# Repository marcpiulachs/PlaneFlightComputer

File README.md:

# Flight Computer

This project is a flight computer powered by an ESP32-C3 microcontroller, designed to control two motors and two servos. It integrates multiple sensors and supports a range of functionalities that make it suitable for small UAVs and drones. The system is designed to operate on a 300mAh LiPo battery, with built-in charging through USB-C.

## Features

- **ESP32-C3** microcontroller for reliable performance and wireless connectivity.
- **Motor Control:**
  - Motor 1: GPIO4
  - Motor 2: GPIO5
- **Servo Control:**
  - Servo 1: GPIO1
  - Servo 2: GPIO6
- **Sensors:**
  - **MAX17048G** (Fuel Gauge) on Address: `0x36` (00110110b)
  - **BMP388** (Barometric Pressure) on Address: `0x76` (1001100b)
  - **QMC5883L** (Magnetometer) on Address: `0x0d` (0001101b)
  - **ICM-42670-P** (6-axis IMU) on Address: `0x68` (1101000b)
- **LEDs:**
  - Internal LED: GPIO7
  - External LED: GPIO0
- **Battery:**
  - Recommended battery: **300mAh LiPo** for optimal performance
  - **USB-C charging** support for ease of use

## Recommended Hardware

- **Battery:** 300mAh LiPo
- **USB-C charger** (included)

## Pinout

| Component      | GPIO Pin  | Description                      |
|----------------|-----------|----------------------------------|
| Motor 1        | GPIO4     | Motor driver pin                 |
| Motor 2        | GPIO5     | Motor driver pin                 |
| Servo 1        | GPIO1     | Servo control pin                |
| Servo 2        | GPIO6     | Servo control pin                |
| Internal LED   | GPIO7     | Status indicator                 |
| External LED   | GPIO0     | Additional LED indicator         |
| MAX17048G      | I2C (0x36)| Fuel gauge sensor                |
| BMP388         | I2C (0x76)| Barometric pressure sensor       |
| QMC5883L       | I2C (0x0d)| Magnetometer sensor              |
| ICM-42670-P    | I2C (0x68)| 6-axis IMU sensor                |

## Power Management

The flight computer operates on a **300mAh LiPo battery**, which provides sufficient power for typical operations. For convenience, the board features **USB-C charging**, allowing you to charge the battery easily.

## Getting Started

To get started with the flight computer:

1. Connect the appropriate motors, servos, and sensors as listed in the pinout table.
2. Power the device using a 300mAh LiPo battery.
3. Use the onboard USB-C port to charge the battery when needed.

## License

This project is open source and available under the [MIT License](LICENSE).

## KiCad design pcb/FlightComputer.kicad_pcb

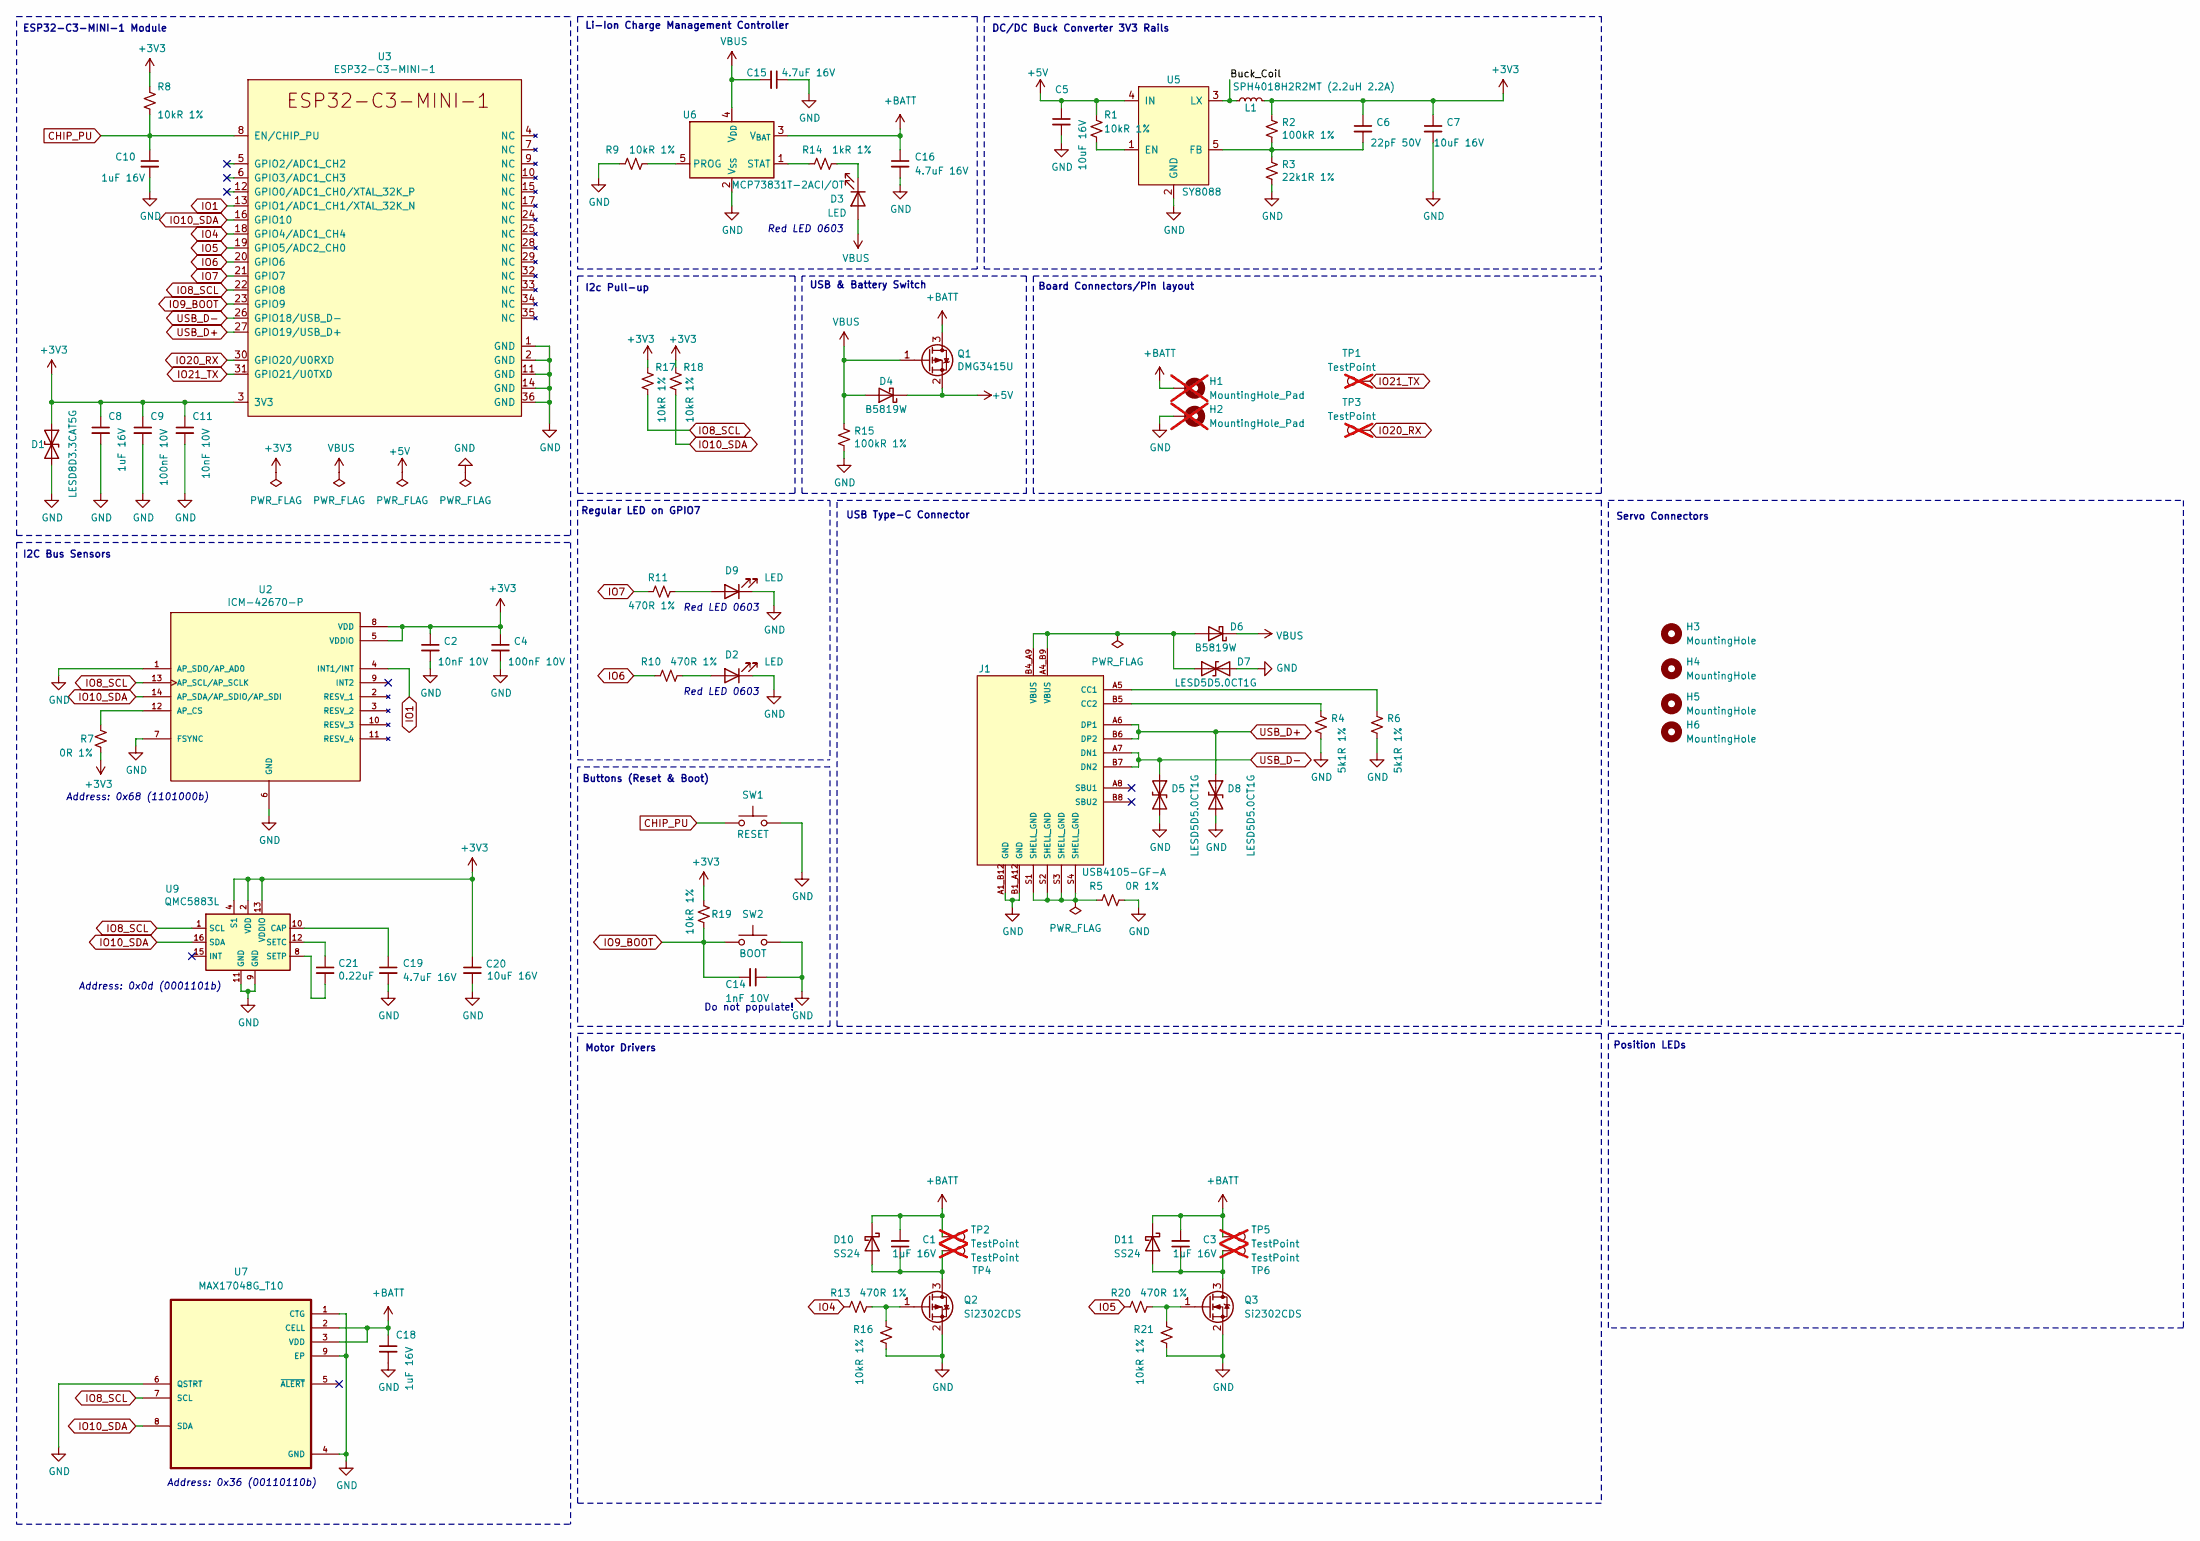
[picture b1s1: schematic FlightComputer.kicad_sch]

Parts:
C1, C3, C8, C10, C18: 1uF 16V; C_0402_1005Metric; LCSC C52923
C2, C11: 10nF 10V; C_0402_1005Metric; LCSC C15195
C4, C9: 100nF 10V; C_0402_1005Metric; LCSC C1525
C5, C7, C20: 10uF 16V; C_0805_2012Metric; LCSC C15850
C6: 22pF 50V; C_0603_1608Metric; LCSC C1653
C14: 1nF 10V; C_0402_1005Metric; LCSC C1523
C15, C16, C19: 4.7uF 16V; C_0603_1608Metric; LCSC C19666
C21: 0.22uF; C_0402_1005Metric; LCSC C16772
D1: LESD8D3.3CAT5G; D_SOD-882; LCSC C172409
D2, D3, D9: LED; LED_0603_1608Metric; LCSC C2286
D4, D6: B5819W; D_SOD-123; LCSC C8598
D5, D7, D8: LESD5D5.0CT1G; D_SOD-523; LCSC C383211
D10, D11: SS24; D_SOD-123; LCSC C5380709
H1, H2: MountingHole_Pad; TestPoint_Pad_D2.0mm; not fitted
H3, H4, H5, H6: MountingHole; MountingHole_2.2mm_M2_DIN965
J1: USB4105-GF-A; GCT_USB4105-GF-A; PARTREV A3; LCSC C165948
L1: SPH4018H2R2MT (2.2uH 2.2A); L_Bourns-SRN4018; LCSC C370436
Q1: DMG3415U; SOT-23; LCSC C96616
Q2, Q3: Si2302CDS; SOT-23; LCSC C10488
R1, R8, R9, R16, R17, R18, R19, R21: 10kR 1%; R_0402_1005Metric; LCSC C25744
R2, R15: 100kR 1%; R_0402_1005Metric; LCSC C25741
R3: 22k1R 1%; R_0402_1005Metric; LCSC C43473
R4, R6: 5k1R 1%; R_0402_1005Metric; LCSC C25905
R5, R7: 0R 1%; R_0402_1005Metric; LCSC C17168
R10, R11, R13, R20: 470R 1%; R_0402_1005Metric; LCSC C25117
R14: 1kR 1%; R_0402_1005Metric; LCSC C11702
SW1: RESET; SW_SPST_PTS810; LCSC C116501
SW2: BOOT; SW_SPST_PTS810; LCSC C116501
TP1, TP3: TestPoint; TestPoint_Pad_D1.0mm; not fitted
TP2, TP4, TP5, TP6: TestPoint; TestPoint_Pad_D2.0mm; not fitted
U2: ICM-42670-P; LGA-14_3x2.5mm_P0.5mm_LayoutBorder3x4y; PARTREV 1.0; LCSC C3288646
U3: ESP32-C3-MINI-1; LCSC C2838502
U5: SY8088; SOT-23-5; LCSC C479072
U6: MCP73831T-2ACI/OT; SOT-23-5; LCSC C424093
U7: MAX17048G_T10; TDFN-8-1EP_2x2mm_P0.5mm_EP0.8x1.2mm; LCSC C2682616
U9: QMC5883L; LGA-16_3x3mm_P0.5mm; LCSC C976032

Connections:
+3V3: C2.1, C4.1, C6.1, C7.1, C8.1, C9.1, C11.1, C20.1, D1.1 (A1), L1.2, R2.1, R7.2, R8.1, R17.1, R18.1, R19.1, U2.5 (VDDIO), U2.8 (VDD), U3.3 (3V3), U9.2 (VDD), U9.4 (S1), U9.13 (VDDIO)
+5V: C5.1, D4.1 (K), Q1.2 (S), R1.1, U5.4 (IN)
+BATT: C1.2, C3.2, C16.1, C18.1, D10.1 (K), D11.1 (K), H1.1, Q1.3 (D), TP2.1, TP5.1, U6.3 (V_{BAT}), U7.2 (CELL), U7.3 (VDD)
/Buck_Coil: L1.1, U5.3 (LX)
CHIP_PU: C10.1, R8.2, SW1.1, U3.8 (EN/CHIP_PU)
GND: C2.2, C4.2, C5.2, C7.2, C8.2, C9.2, C10.2, C11.2, C14.1, C15.1, C16.2, C18.2, C19.2, C20.2, D1.2 (A2), D2.1 (K), D5.2 (A2), D7.2 (A2), D8.2 (A2), D9.1 (K), H2.1, J1.A1_B12 (GND), J1.B1_A12 (GND), Q2.2 (S), Q3.2 (S), R3.2, R4.2, R5.2, R6.2, R9.1, R15.2, R16.2, R21.2, SW1.2, SW2.2, U2.1 (AP_SDO/AP_AD0), U2.6 (GND), U2.7 (FSYNC), U3.1 (GND), U3.2 (GND), U3.11 (GND), U3.14 (GND), U3.36 (GND), U5.2 (GND), U6.2 (V_{SS}), U7.1 (CTG), U7.4 (GND), U7.6 (QSTRT), U7.9 (EP), U9.9 (GND), U9.11 (GND)
IO4: R13.1, U3.18 (GPIO4/ADC1_CH4)
IO5: R20.1, U3.19 (GPIO5/ADC2_CH0)
IO6: R10.1, U3.20 (GPIO6)
IO7: R11.1, U3.21 (GPIO7)
IO8_SCL: R17.2, U2.13 (AP_SCL/AP_SCLK), U3.22 (GPIO8), U7.7 (SCL), U9.1 (SCL)
IO9_BOOT: C14.2, R19.2, SW2.1, U3.23 (GPIO9)
IO10_SDA: R18.2, U2.14 (AP_SDA/AP_SDIO/AP_SDI), U3.16 (GPIO10), U7.8 (SDA), U9.16 (SDA)
IO13: U2.4 (INT1/INT), U3.13 (GPIO1/ADC1_CH1/XTAL_32K_N)
IO20_RX: TP3.1, U3.30 (GPIO20/U0RXD)
IO21_TX: TP1.1, U3.31 (GPIO21/U0TXD)
unnamed: D2.2 (A), R10.2
unnamed: D3.1 (K), R14.2
unnamed: D6.2 (A), D7.1 (A1), J1.A4_B9 (VBUS), J1.B4_A9 (VBUS)
unnamed: D9.2 (A), R11.2
unnamed: C1.1, D10.2 (A), Q2.3 (D), TP4.1
unnamed: C3.1, D11.2 (A), Q3.3 (D), TP6.1
unnamed: J1.A5 (CC1), R6.1
unnamed: J1.B5 (CC2), R4.1
unnamed: J1.S1 (SHELL_GND), J1.S2 (SHELL_GND), J1.S3 (SHELL_GND), J1.S4 (SHELL_GND), R5.1
unnamed: Q2.1 (G), R13.2, R16.1
unnamed: Q3.1 (G), R20.2, R21.1
unnamed: R7.1, U2.12 (AP_CS)
unnamed: R1.2, U5.1 (EN)
unnamed: C6.2, R2.2, R3.1, U5.5 (FB)
unnamed: R9.2, U6.5 (PROG)
unnamed: R14.1, U6.1 (STAT)
unnamed: C19.1, U9.10 (CAP)
unnamed: C21.1, U9.12 (SETC)
unnamed: C21.2, U9.8 (SETP)
USB_D+: D8.1 (A1), J1.A6 (DP1), J1.B6 (DP2), U3.27 (GPIO19/USB_D+)
USB_D-: D5.1 (A1), J1.A7 (DN1), J1.B7 (DN2), U3.26 (GPIO18/USB_D-)
VBUS: C15.2, D3.2 (A), D4.2 (A), D6.1 (K), Q1.1 (G), R15.1, U6.4 (V_{DD})

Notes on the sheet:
USB Type-C Connector
Do not populate!
Buttons (Reset & Boot)
Servo Connectors
Red LED 0603
Motor Drivers
I2c Pull-up
DC/DC Buck Converter 3V3 Rails
USB & Battery Switch
Board Connectors/Pin layout
Address: 0x36 (00110110b)
Address: 0x0d (0001101b)
Regular LED on GPIO7
Position LEDs
Address: 0x68 (1101000b)
ESP32-C3-MINI-1 Module
Li-Ion Charge Management Controller
I2C Bus Sensors

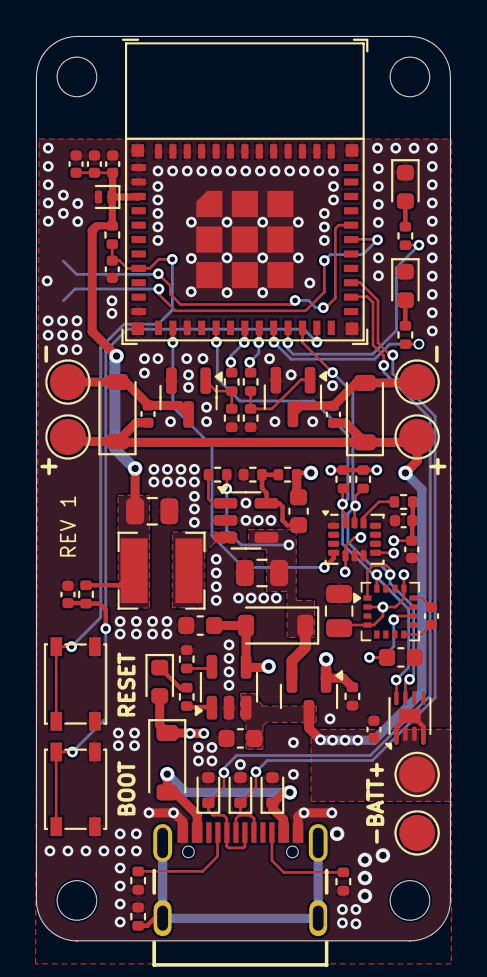
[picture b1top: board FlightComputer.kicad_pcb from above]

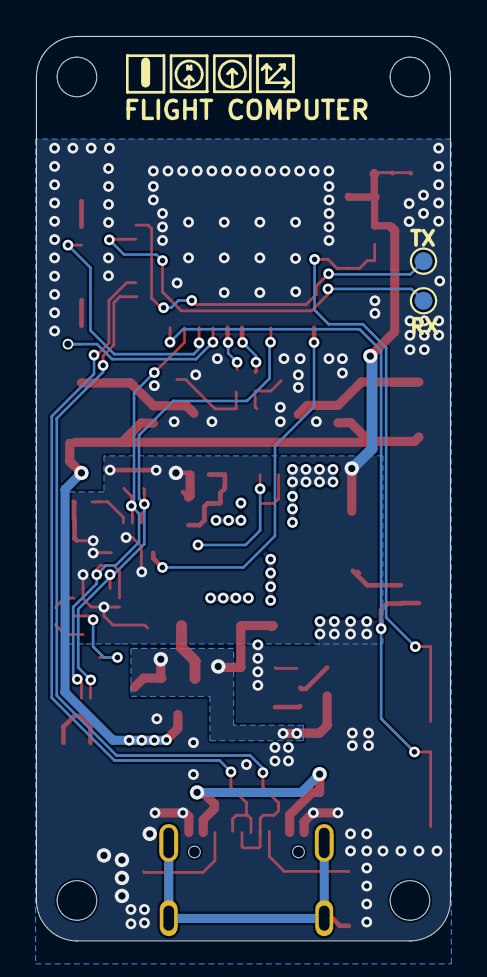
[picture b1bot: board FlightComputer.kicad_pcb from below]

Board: 2 copper layers, 23.0 x 50.2 mm, 74 parts (2 on the bottom side), 38 nets.

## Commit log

2024-09-06 Remove assets
2024-09-06 Remove production files
2024-09-06 Port kicad 8.0
2024-09-06 Clean up, update symbols and footprints, port to Kicad 8.0
2024-09-06 Solve remaining errors and warnings
2024-09-06 Update package
2024-09-06 Clean up not used footprints
2024-09-06 Add new components
2024-09-10 Work in progress
2024-09-14 Add magnamometer and barometer and rearrange items
2024-09-18 Reorganize PCB, remove piezo, temperature sensor and expansion connections
2024-09-19 Add missing components
2024-09-19 Place components on PCB
2024-09-19 Add missing LCSC parts
2024-09-19 Minor corrections
2024-09-20 Design completed
2024-09-20 Remove unused rust board
2024-09-20 Rename Kicad project, rearrange folder structure
2024-09-20 Rearrange some vias, minor changes
2024-09-25 add BMP388 symbol
2024-09-25 BMP280 > BMP388
2024-09-25 add a few vias, move traces
2024-09-25 Change BMP388 pin to input to reduce warnings
2024-09-25 Correct switch symbol to reduce warnings
2024-09-27 Move resistors
2024-09-27 Rotate servos pinouts
2024-11-28 Remove barometer
2024-12-03 Reduce board size
2024-12-03 change Si2319CDS to Si2302CDS
2024-12-03 Move battery pads to front
2024-12-03 Change label sizes
2024-12-03 Connect IO0 to IMU interrupt
2024-12-04 Hide labels
2024-12-04 Add GND vias, clean up schematic
2024-12-04 clean up zones
